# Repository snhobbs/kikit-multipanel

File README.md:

# kikit-multipanel

This repo includes a CLI tool, helper library, example presets, and example projects for using kikit for multiple designs in a single panel.

This should be able to handle correctly placed selections of different boards.
Some extra board sections will need to be added in if the panel has gaps that are too large.

[Installation](https://github.com/snhobbs/kikit-multipanel/blob/master/docs/installation.rst)

[Contributing](https://github.com/snhobbs/kikit-multipanel/blob/master/docs/contributing.rst)

[Usage](https://github.com/snhobbs/kikit-multipanel/blob/master/docs/contributing.rst)

# usage example
```sh
kikit_multipanel --fname panel.xlsx --out panel.kicad_pcb --preset_f preset.json
```

## Future Developments
+ Add a rectangular packing optimization to autoplace the boards.
+ Centroid file correction
+ Add checking for sections that will be cut off

## Notes
+ If the all outlines are not rectangles then vcuts will fail, mousebites need to be used
+ For multi board panels the boards need to be laid out to fit without large gaps.
+ Check the presets file your using by first using the kikit CLI with one of your boards

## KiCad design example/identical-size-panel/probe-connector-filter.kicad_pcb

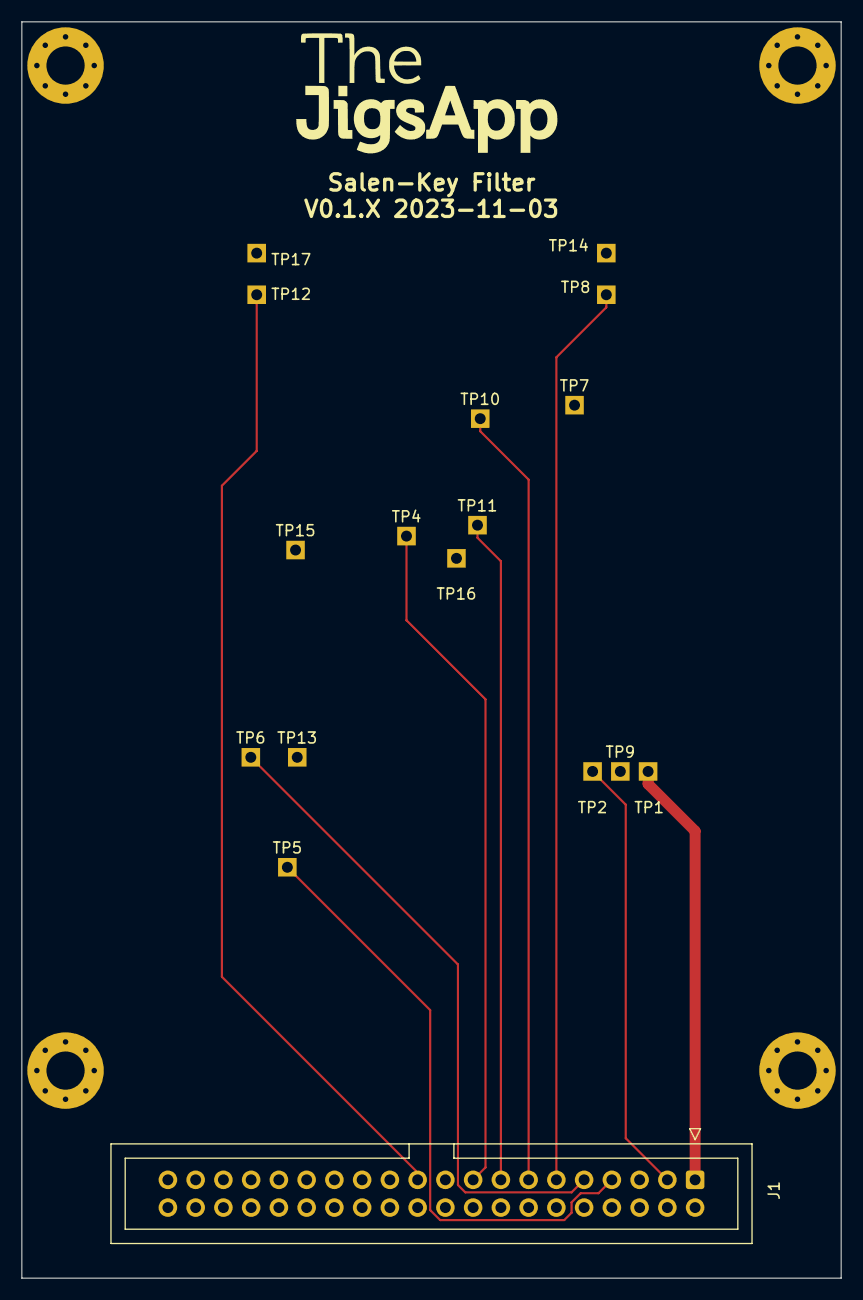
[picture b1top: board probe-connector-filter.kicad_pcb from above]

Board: 2 copper layers, 75.0 x 115.0 mm, 22 parts (0 on the bottom side), 10 nets.

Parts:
BOARD: BOARD; board
J1: Conn_01x40_Female; IDC-Header_2x20_P2.54mm_Vertical
MH1, MH2, MH3, MH4: Conn_01x01_Male; MountingHole_3.5mm_Pad_Via_Paste
TP1: +VIn; R100-2W
TP2: -VIn; R100-2W
TP4: SG2; R100-2W
TP5: VSS; R100-2W
TP6: VDD; R100-2W
TP7, TP9, TP13, TP14, TP15, TP16, TP17: GND; R100-2W
TP8: IN; R100-2W
TP10: SG1; R100-2W
TP11: SG3; R100-2W
TP12: OUT; R100-2W

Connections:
+VIn: J1.1, TP1.1
-VIn: J1.3, TP2.1
GND: J1.2, J1.4, J1.5, J1.6, J1.8, J1.10, J1.12, J1.14, J1.16, J1.18, J1.19, J1.20, J1.22, J1.23, J1.24, J1.25, J1.26, J1.27, J1.28, J1.29, J1.30, J1.31, J1.32, J1.33, J1.34, J1.35, J1.36, J1.37, J1.38, J1.39, J1.40, MH1.1, MH2.1, MH3.1, MH4.1, TP7.1, TP9.1, TP13.1, TP14.1, TP15.1, TP16.1, TP17.1
IN: J1.11, TP8.1
OUT: J1.21, TP12.1
SG1: J1.13, TP10.1
SG2: J1.17, TP4.1
SG3: J1.15, TP11.1
VDD: J1.9, TP6.1
VSS: J1.7, TP5.1

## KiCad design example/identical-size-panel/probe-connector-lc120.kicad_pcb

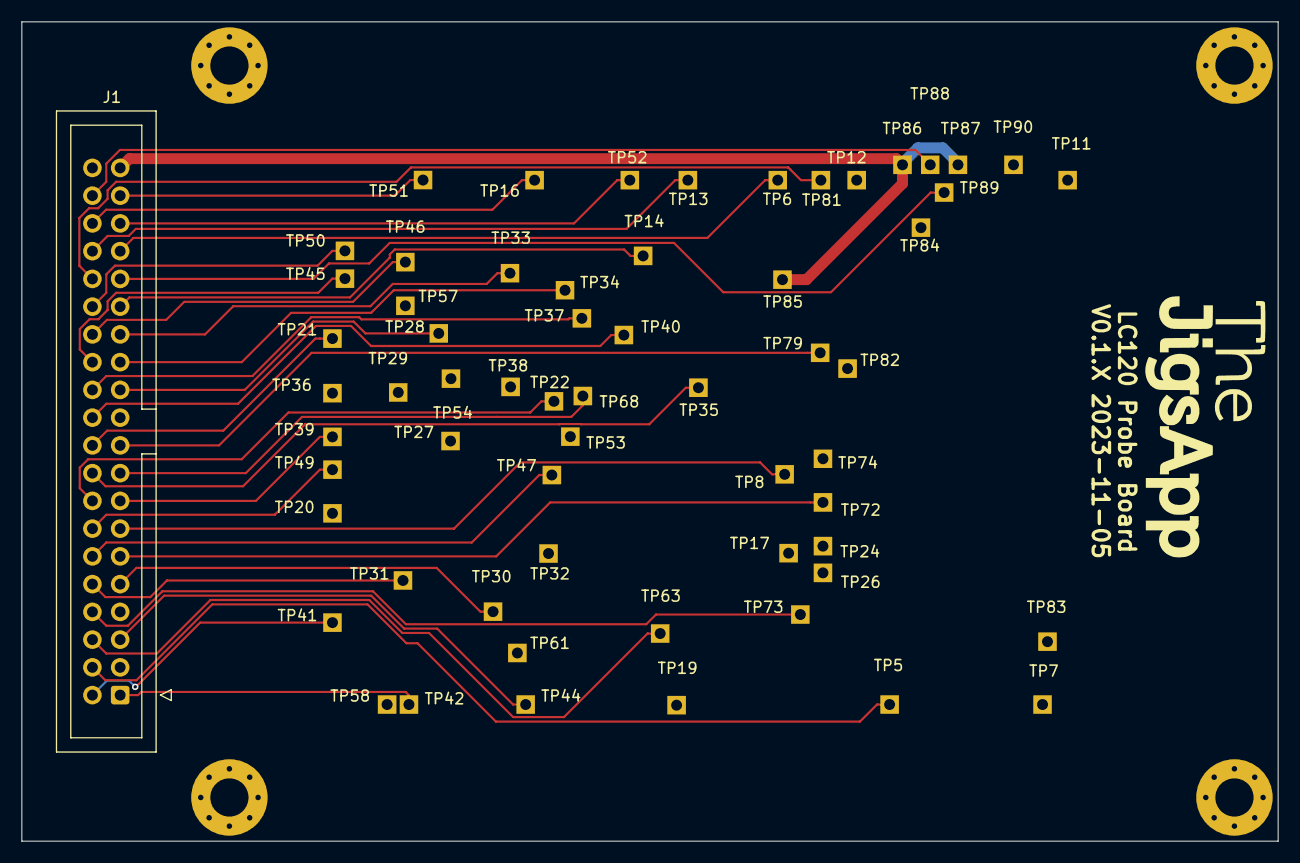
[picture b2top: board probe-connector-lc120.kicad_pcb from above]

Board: 2 copper layers, 115.0 x 75.0 mm, 67 parts (0 on the bottom side), 37 nets.

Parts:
BOARD: BOARD; board
J1: Conn_01x40_Female; IDC-Header_2x20_P2.54mm_Vertical
MH1, MH2, MH3, MH4: Conn_01x01_Male; MountingHole_3.5mm_Pad_Via_Paste
TP5: IPROG_INT; R100-2W
TP6: ILIM-; R100-2W
TP7: TEC-_A; R100-2W
TP8: TEC-; R100-2W
TP11: VMC; R100-2W
TP12: TEC_SUM INT; R100-2W
TP13: ILIM+; R100-2W
TP14: LDEN; R100-2W
TP16: VREF; R100-2W
TP17: VDD; R100-2W
TP19: VCC; R100-2W
TP20: VCCSET; R100-2W
TP21: IPROG; R100-2W
TP22: VCC_TEST; R100-2W
TP24: BUCKEN; R100-2W
TP26: SSYNC; R100-2W
TP27: DVCC; R100-2W
TP28: ~{ISP}; R100-2W
TP29: LDPROG; R100-2W
TP30: URXD; R100-2W
TP31: UTXD; R100-2W
TP32: VDDTEST; R100-2W
TP33: SWDIO; R100-2W
TP34: SWCLK; R100-2W
TP35: ~{TECRUN}; R100-2W
TP36: TSCAL_REF; R100-2W
TP37: RESET; R100-2W
TP38: VSTEST; R100-2W
TP39: TSCAL; R100-2W
TP40: PMON; R100-2W
TP41: D-; R100-2W
TP42: D+; R100-2W
TP44: LDRUN; R100-2W
TP45: SCL; R100-2W
TP46: SDA; R100-2W
TP47: ~{LDON}; R100-2W
TP49: TEMP; R100-2W
TP50: DPOT V-; R100-2W
TP51: WIPER; R100-2W
TP52: LD VLIM O; R100-2W
TP53: Q5B; R100-2W
TP54: LMON BUF; R100-2W
TP57: VL; R100-2W
TP58: ~{LDLIM} O; R100-2W
TP61: LDPROGF; R100-2W
TP63: LDA; R100-2W
TP68: +2.5; R100-2W
TP72: ITEC; R100-2W
TP73: ~{VS_ON}; R100-2W
TP74: Q9B; R100-2W
TP79: ITEC+ Base; R100-2W
TP81: VLIM; R100-2W
TP82, TP83, TP84, TP90: GND; R100-2W
TP85, TP86, TP87: +5In; R100-2W
TP88: PMON_OUT; R100-2W
TP89: LDEN_IN; R100-2W

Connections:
+2.5: J1.17, TP68.1
+5In: J1.39, TP85.1, TP86.1, TP87.1
D+: J1.1, TP42.1
D-: J1.2, TP41.1
DPOT V-: J1.30, TP50.1
GND: J1.3, J1.7, J1.21, J1.40, MH1.1, MH2.1, MH3.1, MH4.1, TP82.1, TP83.1, TP84.1, TP90.1
ILIM+: J1.34, TP13.1
ILIM-: J1.33, TP6.1
IPROG: J1.20, TP21.1
IPROG_INT: J1.4, TP5.1
ITEC: J1.11, TP72.1
ITEC+ Base: J1.19, TP79.1
LD VLIM O: J1.35, TP52.1
LDA: J1.6, TP63.1
LDEN: J1.29, TP14.1
LDEN_IN: J1.31, TP89.1
LDRUN: J1.5, TP44.1
PMON: J1.22, TP40.1
PMON_OUT: J1.38, TP88.1
SCL: J1.26, TP45.1
SDA: J1.28, TP46.1
SWCLK: J1.25, TP34.1
SWDIO: J1.27, TP33.1
TEC-: J1.13, TP8.1
TEMP: J1.14, TP49.1
TSCAL: J1.15, TP39.1
URXD: J1.9, TP30.1
UTXD: J1.10, TP31.1
VCCTEST: J1.16, TP22.1
VLIM: J1.32, TP81.1
VREF: J1.36, TP16.1
WIPER: J1.37, TP51.1
~ISP: J1.23, TP28.1
~LDON: J1.12, TP47.1
~RESET: J1.24, TP37.1
~TECRUN: J1.18, TP35.1
~VS_ON: J1.8, TP73.1

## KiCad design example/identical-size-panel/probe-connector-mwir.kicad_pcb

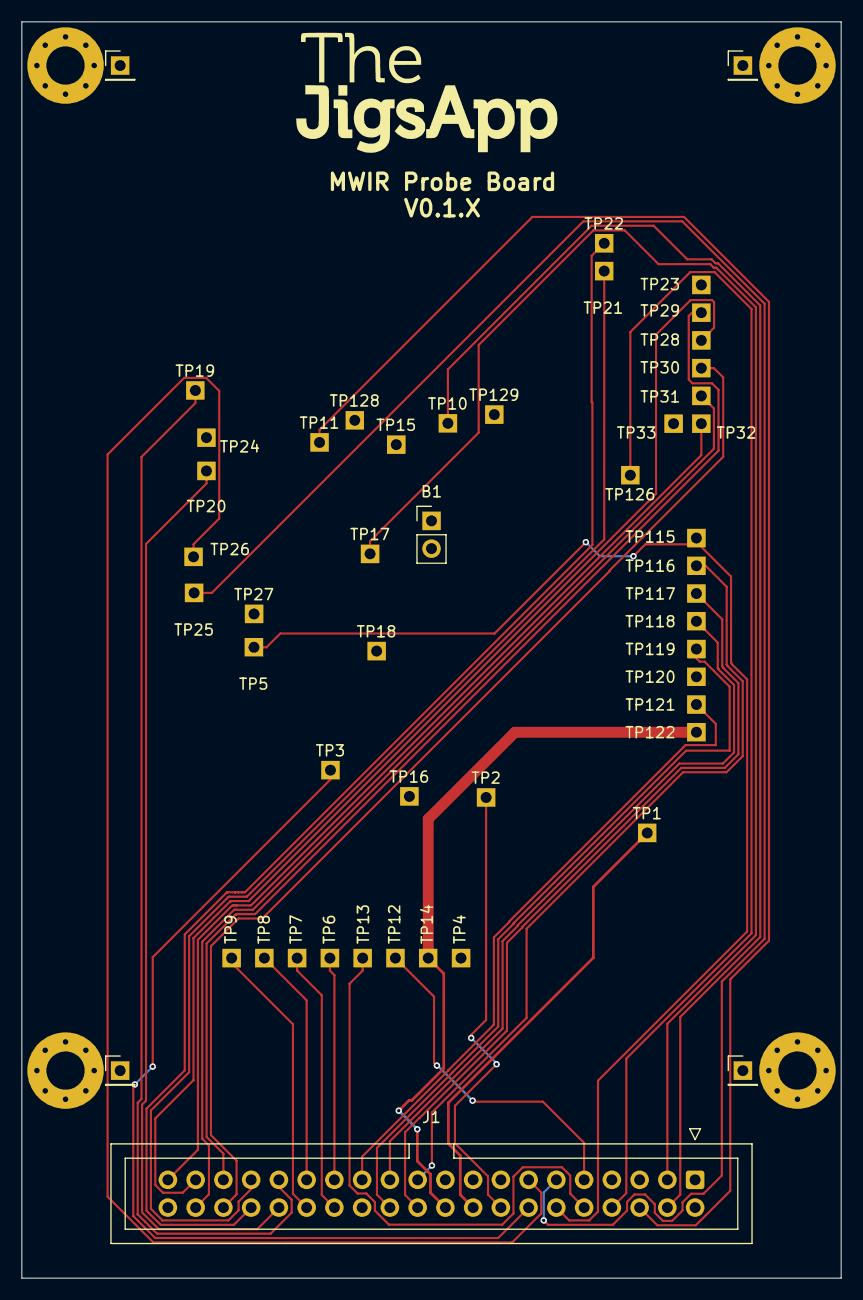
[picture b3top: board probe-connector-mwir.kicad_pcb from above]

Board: 2 copper layers, 75.0 x 115.0 mm, 55 parts (0 on the bottom side), 32 nets.

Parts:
B1: Conn_01x02_Male; PinHeader_1x02_P2.54mm_Vertical
BOARD: BOARD; board
J1: Conn_01x40_Female; IDC-Header_2x20_P2.54mm_Vertical
MH1, MH2, MH3, MH4: Conn_01x01_Male; MountingHole_3.5mm_Pad_Via_Paste
MH5, MH6, MH7, MH8: Conn_01x01_Male; PinHeader_1x01_P2.54mm_Vertical
TP1: +VINF; R100-2W
TP2: +13; R100-2W
TP3: +5; R100-2W
TP4, TP15, TP16, TP18, TP23, TP24, TP27, TP33, TP120, TP128, TP129: GND; R100-2W
TP5, TP115: +3.3; R100-2W
TP6: RX+; R100-2W
TP7: RX-; R100-2W
TP8: TX+; R100-2W
TP9: TX-; R100-2W
TP10: MW0; R100-2W
TP11: MW1; R100-2W
TP12: ANALOG0; R100-2W
TP13: ANALOG1; R100-2W
TP14, TP122: +VIn; R100-2W
TP17: VRefOut; R100-2W
TP19: SWCLK1; R100-2W
TP20: SWDIO1; R100-2W
TP21: SWCLK0; R100-2W
TP22: SWDIO0; R100-2W
TP25: SCL; R100-2W
TP26: SDA; R100-2W
TP28: SDO; R100-2W
TP29: ~{IRQ}; R100-2W
TP30: ~{CS}; R100-2W
TP31: SDI; R100-2W
TP32: SCK; R100-2W
TP116: ~{ISP}{slash}RTS0; R100-2W
TP117: ~{RESET1}; R100-2W
TP118: ~{RESET0}; R100-2W
TP119: RXD0; R100-2W
TP121: TXD0; R100-2W
TP126: MCLK; R100-2W

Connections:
+3.3: J1.12, TP5.1, TP115.1
+5: J1.14, TP3.1
+13: J1.16, TP2.1
+VINF: J1.18, TP1.1
+VIn: J1.20, TP14.1, TP122.1
ANALOG0: J1.9, TP12.1
ANALOG1: J1.10, TP13.1
GND: B1.1, J1.1, J1.2, J1.5, J1.7, J1.15, J1.17, J1.19, J1.26, J1.40, MH1.1, MH2.1, MH3.1, MH4.1, TP4.1, TP15.1, TP16.1, TP18.1, TP23.1, TP24.1, TP27.1, TP33.1, TP120.1, TP128.1, TP129.1
MCLK: J1.8, TP126.1
MW0: J1.4, TP10.1
MW1: J1.6, TP11.1
RX+: J1.27, TP6.1
RX-: J1.28, TP7.1
RXD0: J1.24, TP119.1
SCK: J1.39, TP32.1
SCL: J1.11, TP25.1
SDA: J1.13, TP26.1
SDI: J1.38, TP31.1
SDO: J1.37, TP28.1
SWCLK0: J1.33, TP21.1
SWCLK1: J1.31, TP19.1
SWDIO0: J1.34, TP22.1
SWDIO1: J1.32, TP20.1
TX+: J1.29, TP8.1
TX-: J1.30, TP9.1
TXD0: J1.25, TP121.1
VRefOut: J1.3, TP17.1
~CS: J1.36, TP30.1
~IRQ: J1.35, TP29.1
~ISP/RTS0: J1.21, TP116.1
~RESET0: J1.23, TP118.1
~RESET1: J1.22, TP117.1

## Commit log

2023-11-06 breaking apart script, adding identical size example
2023-11-06 editing readme
2023-11-06 updating modules
2023-11-07 adding images to readme
2023-11-15 add hint how to build docs
2023-11-15 fix typo
2023-11-15 Update .gitmodules to https links
2023-11-15 adding config file for example
2023-11-15 moving kicad-make from gist to repo location
2023-11-24 adding version to cli Bump version: 0.1.0 → 0.1.1
2024-01-02 removing version typo
2024-01-02 Bump version: 0.1.1 → 0.1.2
2024-07-07 repackaging
2024-07-07 fixed doc build
2024-07-11 formatting and changing license to lgpl
2024-09-18 removed docs, unused
